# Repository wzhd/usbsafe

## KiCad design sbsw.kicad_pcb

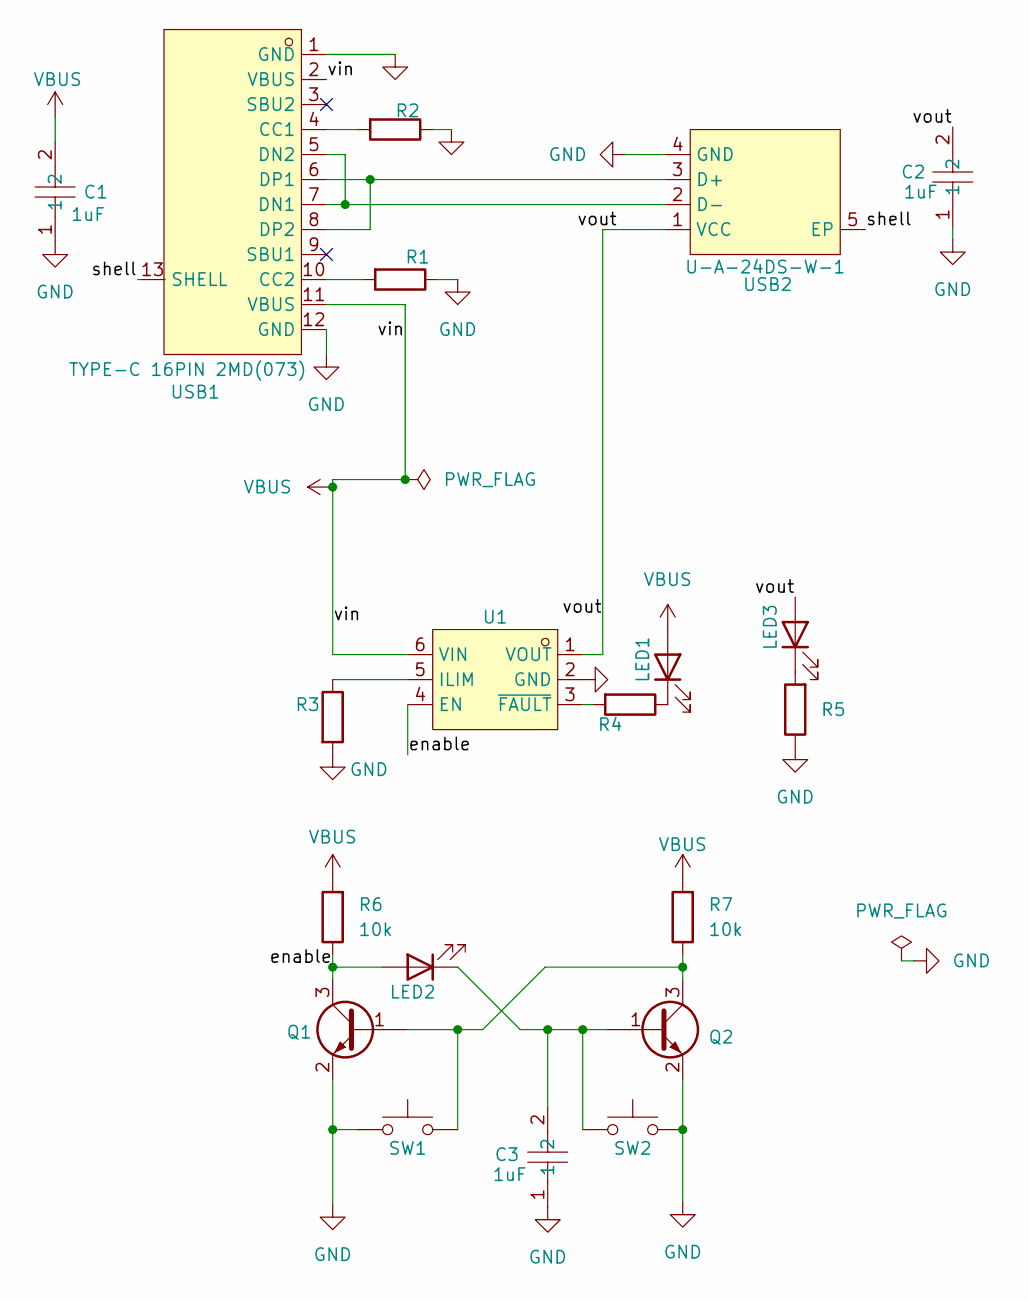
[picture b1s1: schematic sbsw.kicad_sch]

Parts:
C1, C2, C3: 1uF; C_0805_2012Metric; LCSC Part C45783
LED1, LED2, LED3: LED; LED_1206_3216Metric
Q1, Q2: MMBT3904; SOT-23
R1, R2: 5.1k; R_0402_1005Metric
R3: 150k; R_1206_3216Metric
R4: 5k; R_0402_1005Metric
R5: R; R_0402_1005Metric
R6: 10k; R_0402_1005Metric
R7: 10k; R_1206_3216Metric
SW1, SW2: SW_Push; SW_SPST_TL3342
U1: SOT-23-6
USB1: TYPE-C 16PIN 2MD(073); USB-C-SMD_TYPE-C-6PIN-2MD-073; LCSC Part C2765186
USB2: U-A-24DS-W-1; USB-A; LCSC Part C530628

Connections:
/enable: LED2.2 (A), Q1.3 (C), R6.1, U1.4 (EN)
/shell: USB1.13 (SHELL), USB2.5 (EP)
/vout: C2.2, LED3.2 (A), U1.1 (VOUT), USB2.1 (VCC)
GND: C1.1, C2.1, C3.1, Q1.2 (E), Q2.2 (E), R1.1, R2.1, R3.2, R5.1, SW1.1, SW2.2, U1.2 (GND), USB1.1 (GND), USB1.12 (GND), USB2.4 (GND)
unnamed: LED1.1 (K), R4.1
unnamed: C3.2, LED2.1 (K), Q2.1 (B), SW2.1
unnamed: LED3.1 (K), R5.2
unnamed: Q1.1 (B), Q2.3 (C), R7.1, SW1.2
unnamed: R3.1, U1.5 (ILIM)
unnamed: R4.2, U1.3 (~FAULT)
unnamed: R2.2, USB1.4 (CC1)
unnamed: R1.2, USB1.10 (CC2)
unnamed: USB1.5 (DN2), USB1.7 (DN1), USB2.2 (D-)
unnamed: USB1.6 (DP1), USB1.8 (DP2), USB2.3 (D+)
VBUS: C1.2, LED1.2 (A), R6.2, R7.2, U1.6 (VIN), USB1.2 (VBUS), USB1.11 (VBUS)

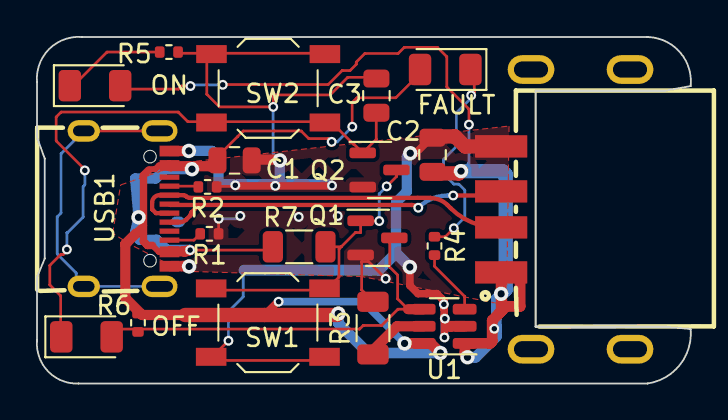
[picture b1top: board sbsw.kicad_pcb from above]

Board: 2 copper layers, 36.3 x 19.2 mm, 20 parts (0 on the bottom side), 15 nets.

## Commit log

2024-04-10 switch
2024-04-10 add libs
